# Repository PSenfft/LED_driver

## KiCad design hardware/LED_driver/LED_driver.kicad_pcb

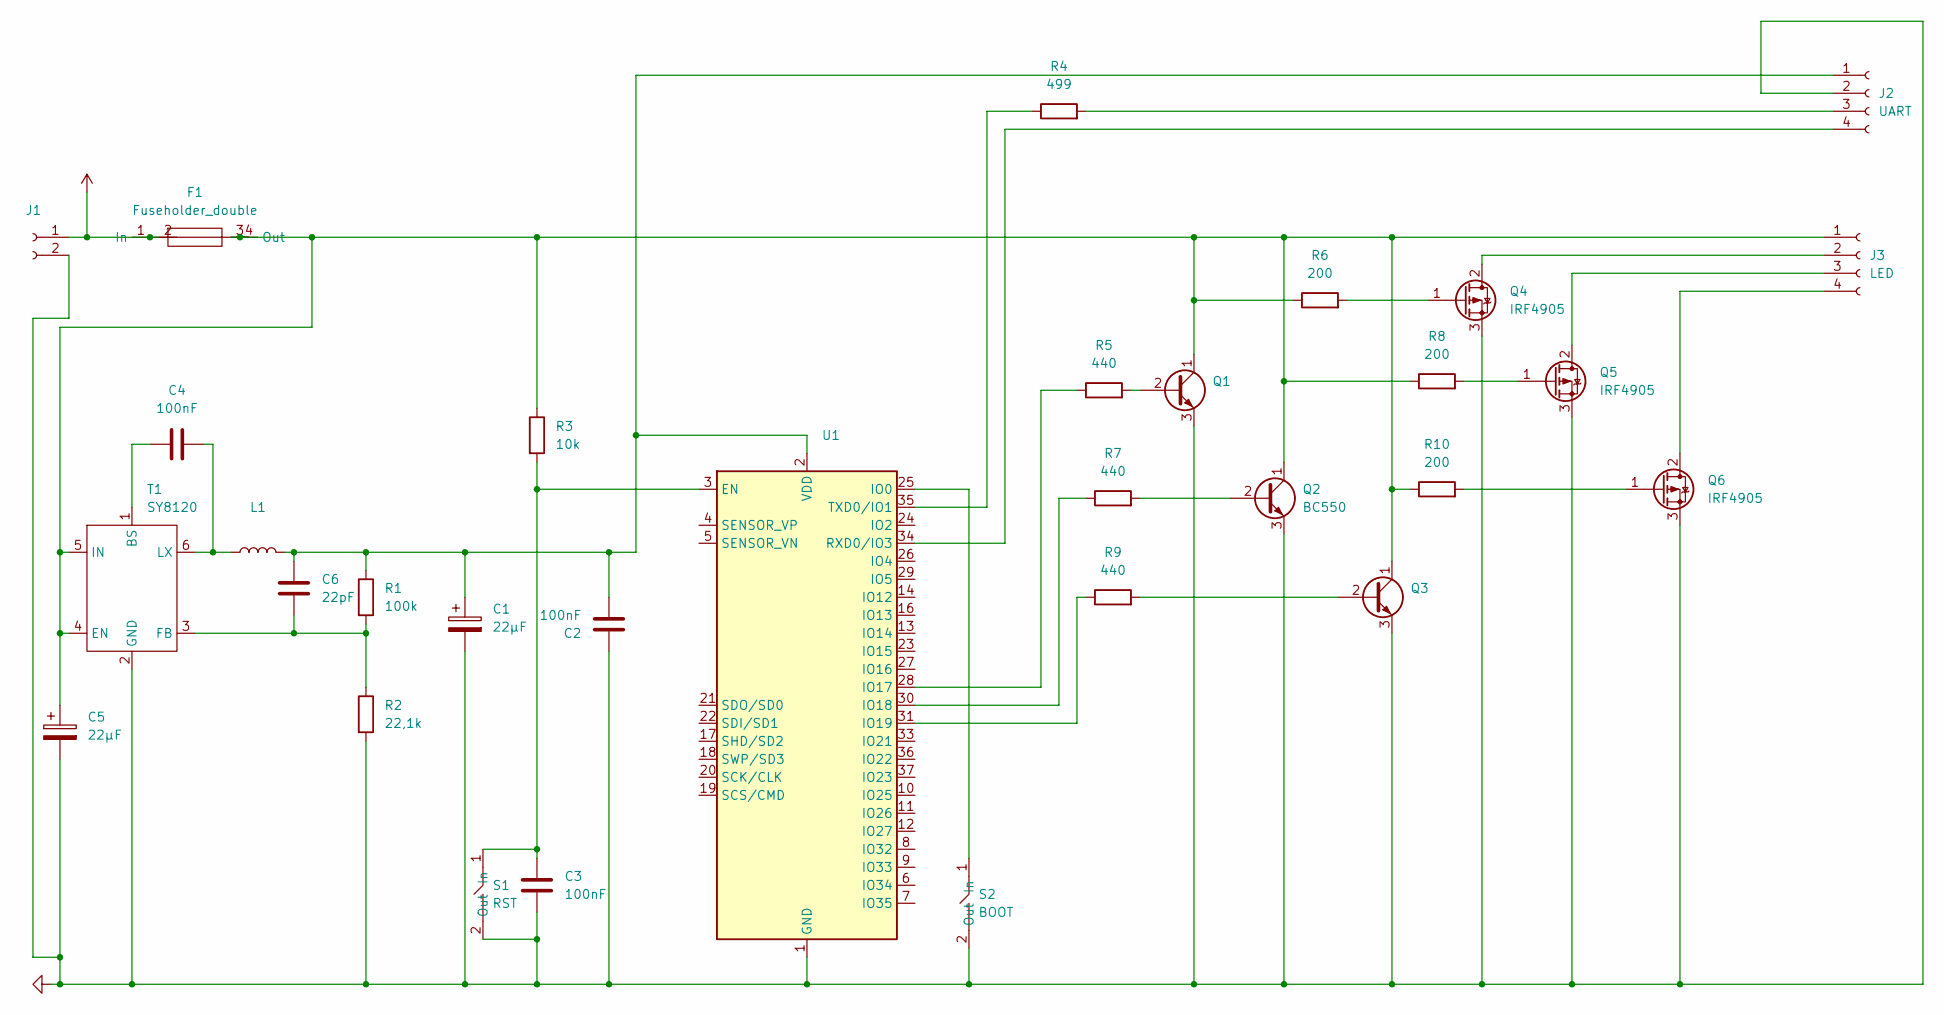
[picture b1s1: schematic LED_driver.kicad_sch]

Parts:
C1, C5: 22µF; CP_Elec_5x5.3
C2, C3, C4: 100nF; C_0603_1608Metric
C6: 22pF; C_0603_1608Metric
F1: Fuseholder_double; Fuseholder 5x20
J1: (no value)
J2: UART; PinHeader_2x02_P2.54mm_Vertical
J3: LED; PinHeader_1x04_P2.54mm_Vertical
L1: (no value)
Q1, Q3: (no value)
Q2: BC550; TO-92
Q4, Q5, Q6: IRF4905; TO-220-3_Vertical
R1: 100k; R_0603_1608Metric
R2: 22,1k; R_0603_1608Metric
R3: 10k; R_0603_1608Metric
R4: 499; R_0603_1608Metric
R5, R7, R9: 440; R_0603_1608Metric
R6, R8, R10: 200; R_0603_1608Metric
S1: RST; SW-SMD-2.9x3.9x1,7
S2: BOOT; SW-SMD-2.9x3.9x1,7
T1: SY8120; SOT-23-6
U1: (no value)

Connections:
unnamed: C3.1, R3.2, S1.1 (In), U1.3 (EN)
unnamed: C4.1, T1.1 (BS)
unnamed: C4.2, L1.1, T1.6 (LX)
unnamed: C5.1, F1.3, F1.4 (Out), J3.1, Q1.1 (C), Q2.1 (C), Q3.1 (C), R3.1, R6.1, R8.1, R10.1, T1.4 (EN), T1.5 (IN)
unnamed: C1.1, C2.2, C6.1, J2.1, L1.2, R1.1, U1.2 (VDD)
unnamed: C6.2, R1.2, R2.1, T1.3 (FB)
unnamed: J2.3, R4.2
unnamed: J2.4, U1.34 (RXD0/IO3)
unnamed: J3.2, Q4.2 (D)
unnamed: J3.3, Q5.2 (D)
unnamed: J3.4, Q6.2 (D)
unnamed: Q1.2 (B), R5.2
unnamed: Q2.2 (B), R7.2
unnamed: Q3.2 (B), R9.2
unnamed: Q4.1 (G), R6.2
unnamed: Q5.1 (G), R8.2
unnamed: Q6.1 (G), R10.2
unnamed: R4.1, U1.35 (TXD0/IO1)
unnamed: R5.1, U1.28 (IO17)
unnamed: R7.1, U1.30 (IO18)
unnamed: R9.1, U1.31 (IO19)
unnamed: S2.1 (In), U1.25 (IO0)

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
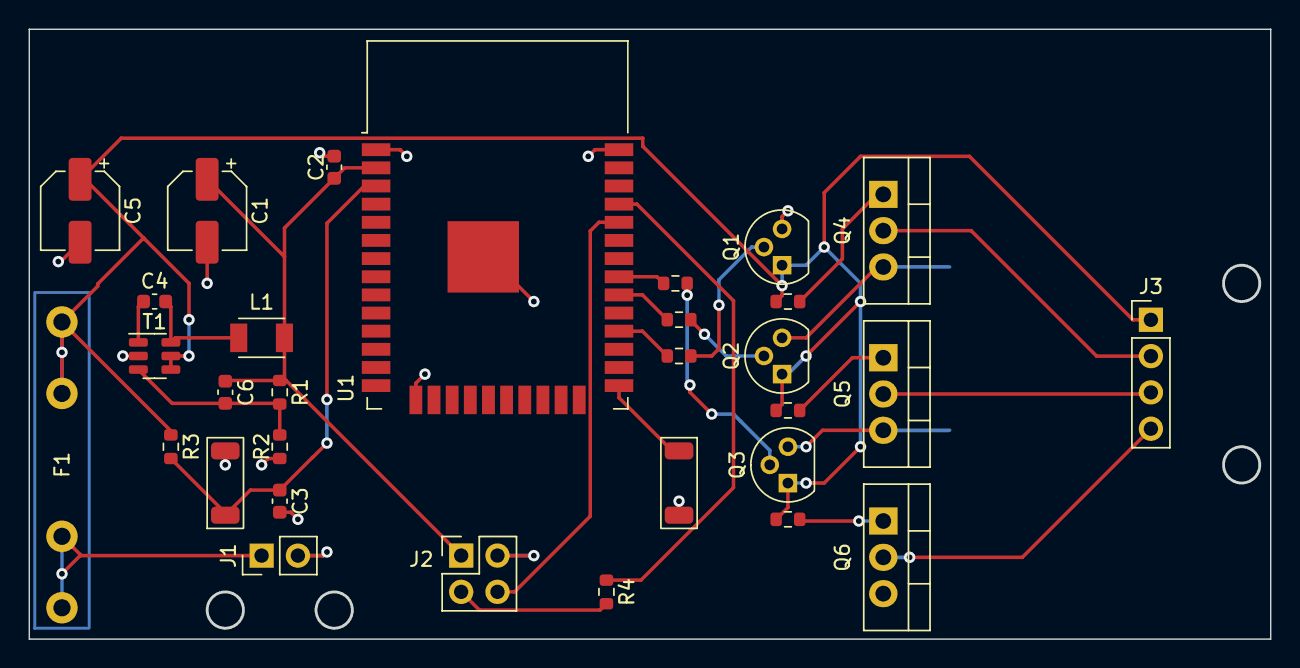
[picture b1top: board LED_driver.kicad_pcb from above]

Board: 2 copper layers, 86.8 x 42.6 mm, 31 parts (0 on the bottom side), 24 nets.

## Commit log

2022-05-18 init
2022-05-18 added datasheets
2022-05-19 programmmin for esp is still not included, not tested
2022-06-14 finished PCB
